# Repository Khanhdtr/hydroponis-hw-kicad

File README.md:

# Hydroponics hardware
Mạch thủy canh thông minh
## Yêu cầu thiết kế
-Nguồn vào 12V DC dùng LM2596 => 5V
- IC dùng module Maple Mini + NodeCMU
- Đọc các giá trị cảm biến DS18b20, Dht11, EC, Bh1750 , water level
- Sử dụng Touchpad key 2x4 để tương tác
- Sử dụng LCD16x2 để hiển thị các thông số cảm biến và trạng thái
- Tương tác với người dùng thông qua giao App Blynk
## Tổng quan
### Sơ đồ nguyên lý

### PCB

### 3D

### TOP

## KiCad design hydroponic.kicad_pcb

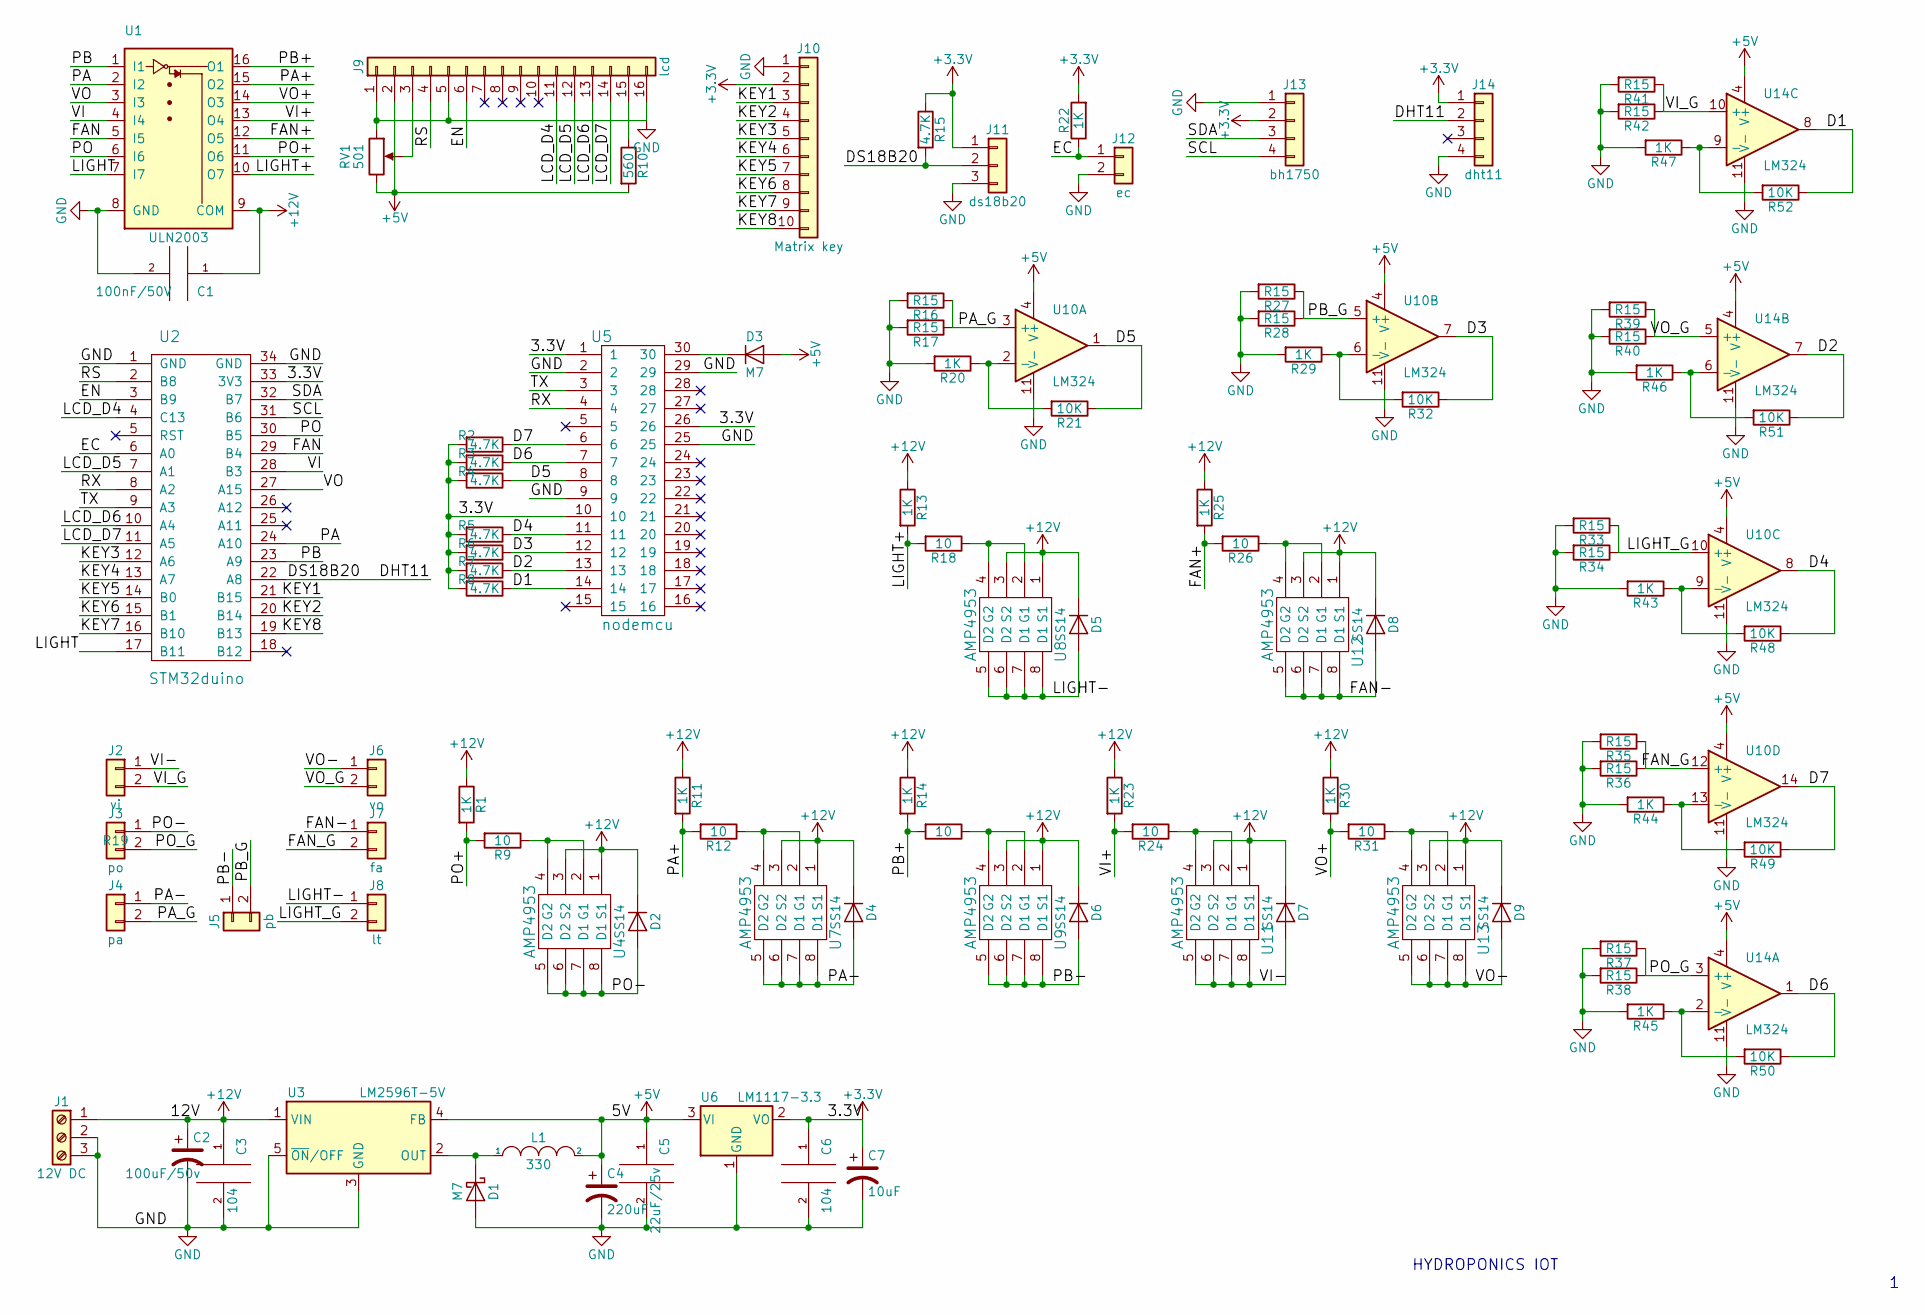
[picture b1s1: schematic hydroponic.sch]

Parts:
C1: 100nF/50V; C_0805_HandSoldering
C2: 100uF/50v; CP_Elec_8x10
C3, C6: 104; C_0805_HandSoldering
C4: 220uF; CP_Elec_8x10
C5: 22uF/25v; C_1210_HandSoldering
C7: 10uF; C_1210_HandSoldering
D1, D3: M7; D_SMB_Handsoldering
D2, D4, D5, D6, D7, D8, D9: SS14; D_SMB_Handsoldering
J1: 12V DC; BARREL_JACK
J2: vi; TerminalBlock_Phoenix_PT-3.5mm_2pol
J3: po; TerminalBlock_Phoenix_PT-3.5mm_2pol
J4: pa; TerminalBlock_Phoenix_PT-3.5mm_2pol
J5: pb; TerminalBlock_Phoenix_PT-3.5mm_2pol
J6: vo; TerminalBlock_Phoenix_PT-3.5mm_2pol
J7: fa; TerminalBlock_Phoenix_PT-3.5mm_2pol
J8: lt; TerminalBlock_Phoenix_PT-3.5mm_2pol
J9: lcd; Pin_Header_Angled_1x16_Pitch2.54mm
J10: Matrix key; Pin_Header_Angled_1x10_Pitch2.54mm
J11: ds18b20; Pin_Header_Angled_1x03_Pitch2.54mm
J12: ec; Pin_Header_Angled_1x02_Pitch2.54mm
J13: bh1750; Pin_Header_Angled_1x04_Pitch2.54mm
J14: dht11; Pin_Header_Angled_1x04_Pitch2.54mm
L1: 330; L_12x12mm_h4.5mm
R1, R11, R13, R14, R20, R22, R23, R25, R29, R30, R43, R44, R45, R46, R47: 1K; R_0805_HandSoldering
R2, R3, R4, R5, R6, R7, R8, R15: 4.7K; R_0805_HandSoldering
R9, R12, R18, R19, R24, R26, R31: 10; R_0805_HandSoldering
R10: 560; R_0805_HandSoldering
R16, R17, R27, R28, R33, R34, R35, R36, R37, R38, R39, R40, R41, R42: R15; R_1210_HandSoldering
R21, R32, R48, R49, R50, R51, R52: 10K; R_0805_HandSoldering
RV1: 501; VARmini
U1: ULN2003; DIP-16_W7.62mm_LongPads
U2: STM32duino; MapleMini
U3: LM2596T-5V; TO-263-5_TabPin3
U4, U7, U8, U9, U11, U12, U13: AMP4953; SOIC-8_3.9x4.9mm_Pitch1.27mm
U5: nodemcu; NodeMCU
U6: LM1117-3.3; SOT-223-3_TabPin2
U10, U14: LM324; SOIC-14_3.9x8.7mm_Pitch1.27mm

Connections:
+3V3: C6.1, C7.1, J10.2, J11.1, J13.2, J14.1, R2.2, R3.2, R4.2, R5.2, R6.2, R7.2, R8.2, R15.1, R22.2, U2.33 (3V3), U5.1, U5.10, U5.26, U6.2 (VO)
+5V: C4.1, C5.1, D3.2 (A), J9.2, L1.2, R10.2, RV1.3, U3.4 (FB), U6.3 (VI), U10.4 (V+), U14.4 (V+)
+12V: C1.1, C2.1, C3.1, D2.1 (K), D4.1 (K), D5.1 (K), D6.1 (K), D7.1 (K), D8.1 (K), D9.1 (K), J1.1, R1.1, R11.1, R13.1, R14.1, R23.1, R25.1, R30.1, U1.9 (COM), U3.1 (VIN), U4.1 (S1), U4.3 (S2), U7.1 (S1), U7.3 (S2), U8.1 (S1), U8.3 (S2), U9.1 (S1), U9.3 (S2), U11.1 (S1), U11.3 (S2), U12.1 (S1), U12.3 (S2), U13.1 (S1), U13.3 (S2)
/D1: R8.1, R52.1, U5.14, U14.8
/D2: R7.1, R51.1, U5.13, U14.7
/D3: R6.1, R32.1, U5.12, U10.7
/D4: R5.1, R48.1, U5.11, U10.8
/D5: R4.1, R21.1, U5.8, U10.1
/D6: R3.1, R50.1, U5.7, U14.1
/D7: R2.1, R49.1, U5.6, U10.14
/DHT11: J11.2, J14.2, R15.2, U2.22 (A8)
/EC: J12.1, R22.1, U2.6 (A0)
/EN: J9.6, U2.3 (B9)
/FAN: U1.5 (I5), U2.29 (B4)
/FAN+: R25.2, R26.2, U1.12 (O5)
/FAN-: D8.2 (A), J7.1, U12.5 (D2), U12.6 (D2), U12.7 (D1), U12.8 (D1)
/FAN_G: J7.2, R35.1, R36.1, U10.12 (+)
/KEY1: J10.3, U2.21 (B15)
/KEY2: J10.4, U2.20 (B14)
/KEY3: J10.5, U2.12 (A6)
/KEY4: J10.6, U2.13 (A7)
/KEY5: J10.7, U2.14 (B0)
/KEY6: J10.8, U2.15 (B1)
/KEY7: J10.9, U2.16 (B10)
/KEY8: J10.10, U2.19 (B13)
/LCD_D4: J9.11, U2.4 (C13)
/LCD_D5: J9.12, U2.7 (A1)
/LCD_D6: J9.13, U2.10 (A4)
/LCD_D7: J9.14, U2.11 (A5)
/LIGHT: U1.7 (I7), U2.17 (B11)
/LIGHT+: R13.2, R18.2, U1.10 (O7)
/LIGHT-: D5.2 (A), J8.1, U8.5 (D2), U8.6 (D2), U8.7 (D1), U8.8 (D1)
/LIGHT_G: J8.2, R33.1, R34.1, U10.10 (+)
/PA: U1.2 (I2), U2.24 (A10)
/PA+: R11.2, R12.2, U1.15 (O2)
/PA-: D4.2 (A), J4.1, U7.5 (D2), U7.6 (D2), U7.7 (D1), U7.8 (D1)
/PA_G: J4.2, R16.1, R17.1, U10.3 (+)
/PB: U1.1 (I1), U2.23 (A9)
/PB+: R14.2, R19.2, U1.16 (O1)
/PB-: D6.2 (A), J5.1, U9.5 (D2), U9.6 (D2), U9.7 (D1), U9.8 (D1)
/PB_G: J5.2, R27.1, R28.1, U10.5 (+)
/PO: U1.6 (I6), U2.30 (B5)
/PO+: R1.2, R9.2, U1.11 (O6)
/PO-: D2.2 (A), J3.1, U4.5 (D2), U4.6 (D2), U4.7 (D1), U4.8 (D1)
/PO_G: J3.2, R37.1, R38.1, U14.3 (+)
/RS: J9.4, U2.2 (B8)
/RX: U2.8 (A2), U5.4
/SCL: J13.4, U2.31 (B6)
/SDA: J13.3, U2.32 (B7)
/TX: U2.9 (A3), U5.3
/VI: U1.4 (I4), U2.28 (B3)
/VI+: R23.2, R24.2, U1.13 (O4)
/VI-: D7.2 (A), J2.1, U11.5 (D2), U11.6 (D2), U11.7 (D1), U11.8 (D1)
/VI_G: J2.2, R41.1, R42.1, U14.10 (+)
/VO: U1.3 (I3), U2.27 (A15)
/VO+: R30.2, R31.2, U1.14 (O3)
/VO-: D9.2 (A), J6.1, U13.5 (D2), U13.6 (D2), U13.7 (D1), U13.8 (D1)
/VO_G: J6.2, R39.1, R40.1, U14.5 (+)
GND: C1.2, C2.2, C3.2, C4.2, C5.2, C6.2, C7.2, D1.2 (A), J1.2, J1.3, J9.1, J9.5, J9.16, J10.1, J11.3, J12.2, J13.1, J14.4, R16.2, R17.2, R20.2, R27.2, R28.2, R29.2, R33.2, R34.2, R35.2, R36.2, R37.2, R38.2, R39.2, R40.2, R41.2, R42.2, R43.2, R44.2, R45.2, R46.2, R47.2, RV1.1, U1.8 (GND), U2.1 (GND), U2.34 (GND), U3.3 (GND), U3.5 (~ON~/OFF), U5.2, U5.9, U5.25, U5.29, U6.1 (GND), U10.11 (V-), U14.11 (V-)
unnamed: D1.1 (K), L1.1, U3.2 (OUT)
unnamed: D3.1 (K), U5.30
unnamed: J9.3, RV1.2
unnamed: J9.15, R10.1
unnamed: R9.1, U4.2 (G1), U4.4 (G2)
unnamed: R12.1, U7.2 (G1), U7.4 (G2)
unnamed: R18.1, U8.2 (G1), U8.4 (G2)
unnamed: R19.1, U9.2 (G1), U9.4 (G2)
unnamed: R20.1, R21.2, U10.2 (-)
unnamed: R24.1, U11.2 (G1), U11.4 (G2)
unnamed: R26.1, U12.2 (G1), U12.4 (G2)
unnamed: R29.1, R32.2, U10.6 (-)
unnamed: R31.1, U13.2 (G1), U13.4 (G2)
unnamed: R43.1, R48.2, U10.9 (-)
unnamed: R44.1, R49.2, U10.13 (-)
unnamed: R45.1, R50.2, U14.2 (-)
unnamed: R46.1, R51.2, U14.6 (-)
unnamed: R47.1, R52.2, U14.9 (-)

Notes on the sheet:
HYDROPONICS IOT

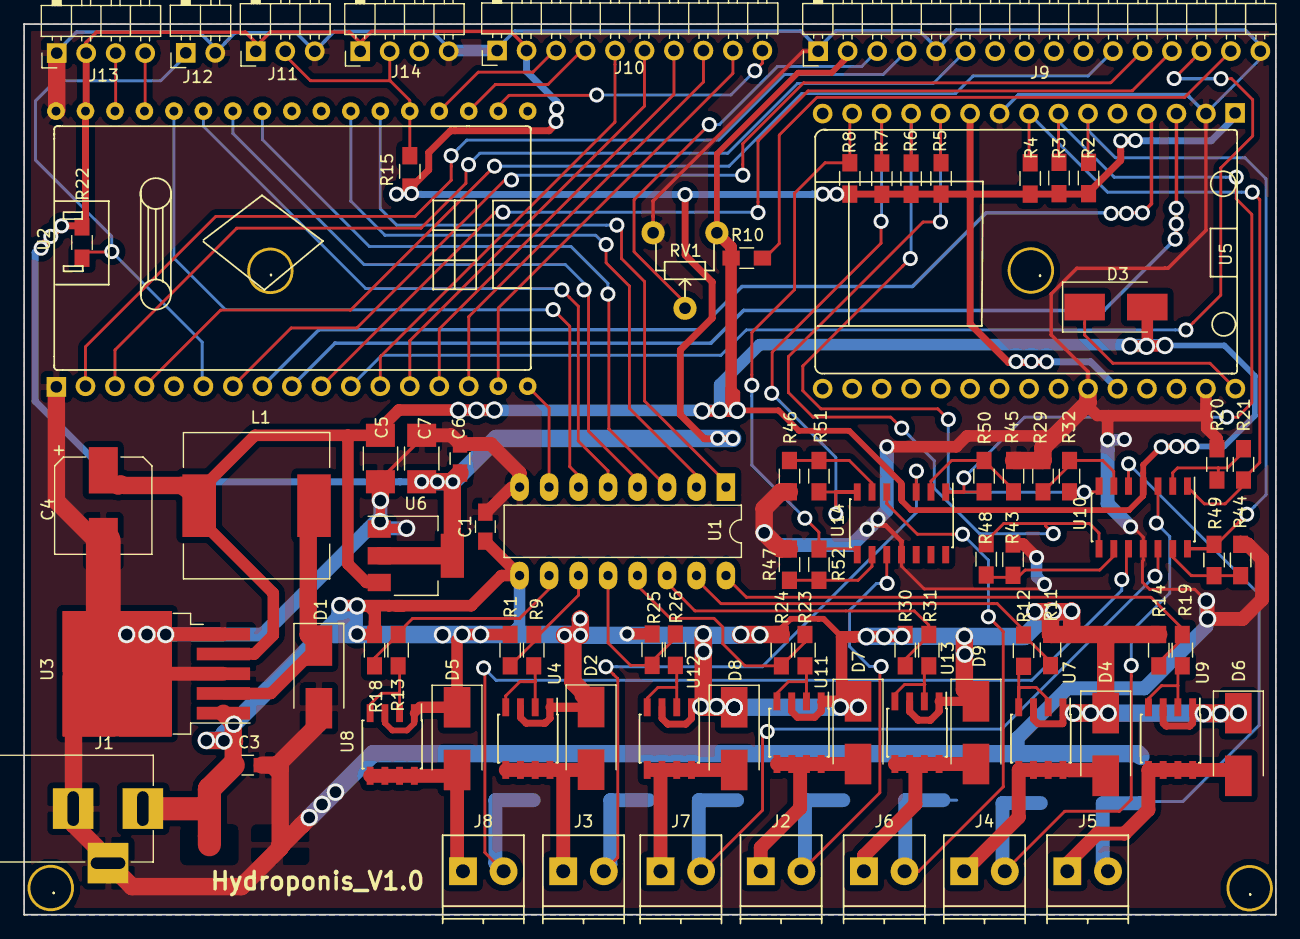
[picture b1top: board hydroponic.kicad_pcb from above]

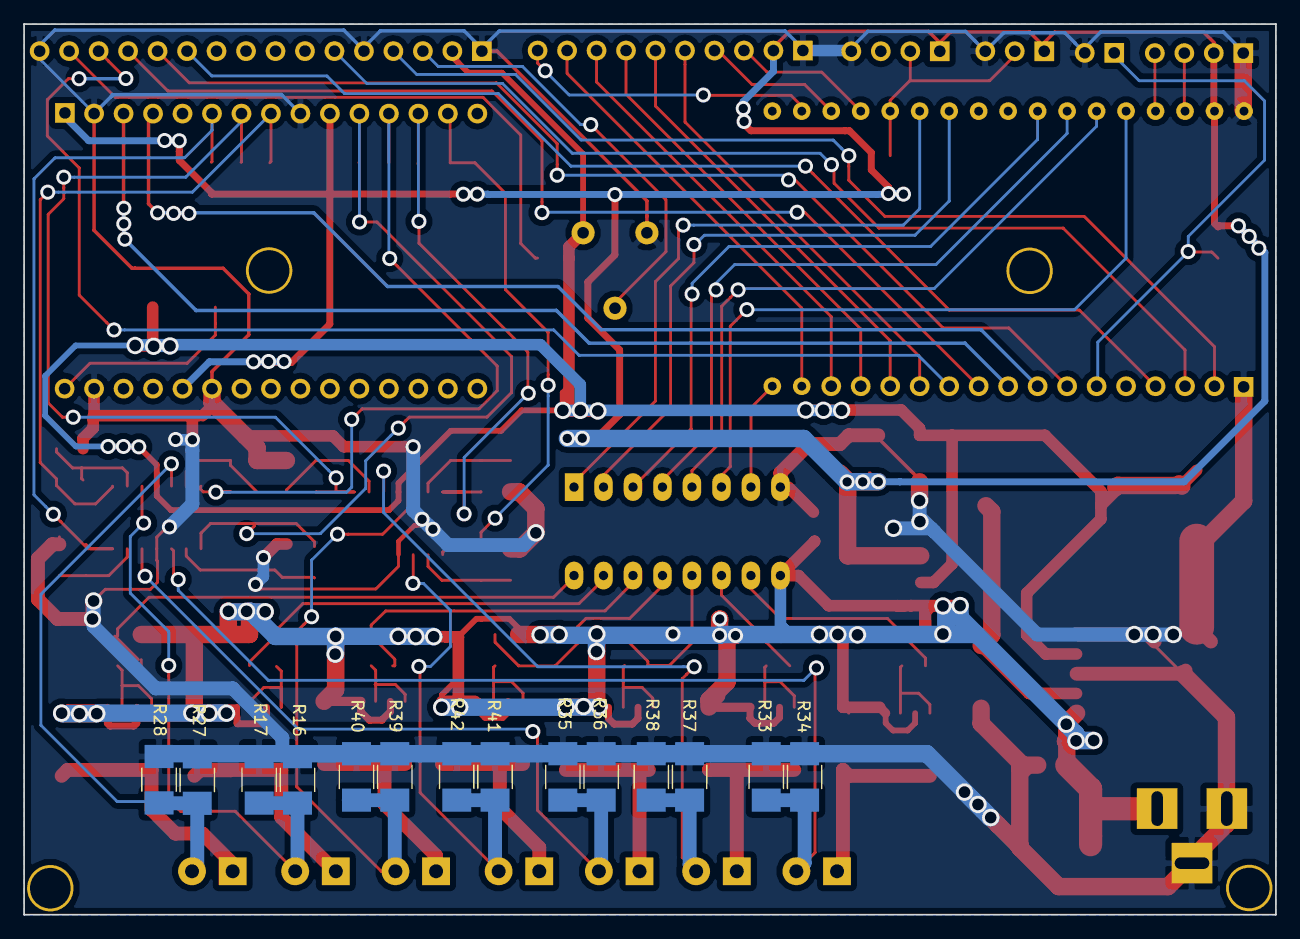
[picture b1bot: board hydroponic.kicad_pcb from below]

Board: 2 copper layers, 107.8 x 76.7 mm, 101 parts (14 on the bottom side), 77 nets.

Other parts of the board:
., .#2, .#3, .#4: Drill_3.5mm

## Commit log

2017-12-27 initial hydroponics hardware
2017-12-27 add asset,gitignore, readme.md
2017-12-27 edit readme
2017-12-28 add net 12v to AMP4953
2017-12-28 edit all power in pcb
2017-12-28 edit all net in pcb
2017-12-28 add gerber file
2018-03-07 add toop.jjpg
